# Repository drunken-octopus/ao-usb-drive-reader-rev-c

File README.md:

# ao-usb-drive-reader-rev-c
Revision C of the Aleph Objects USB reader ("green"), as originally archived from AlephObject's git repos in 2019.

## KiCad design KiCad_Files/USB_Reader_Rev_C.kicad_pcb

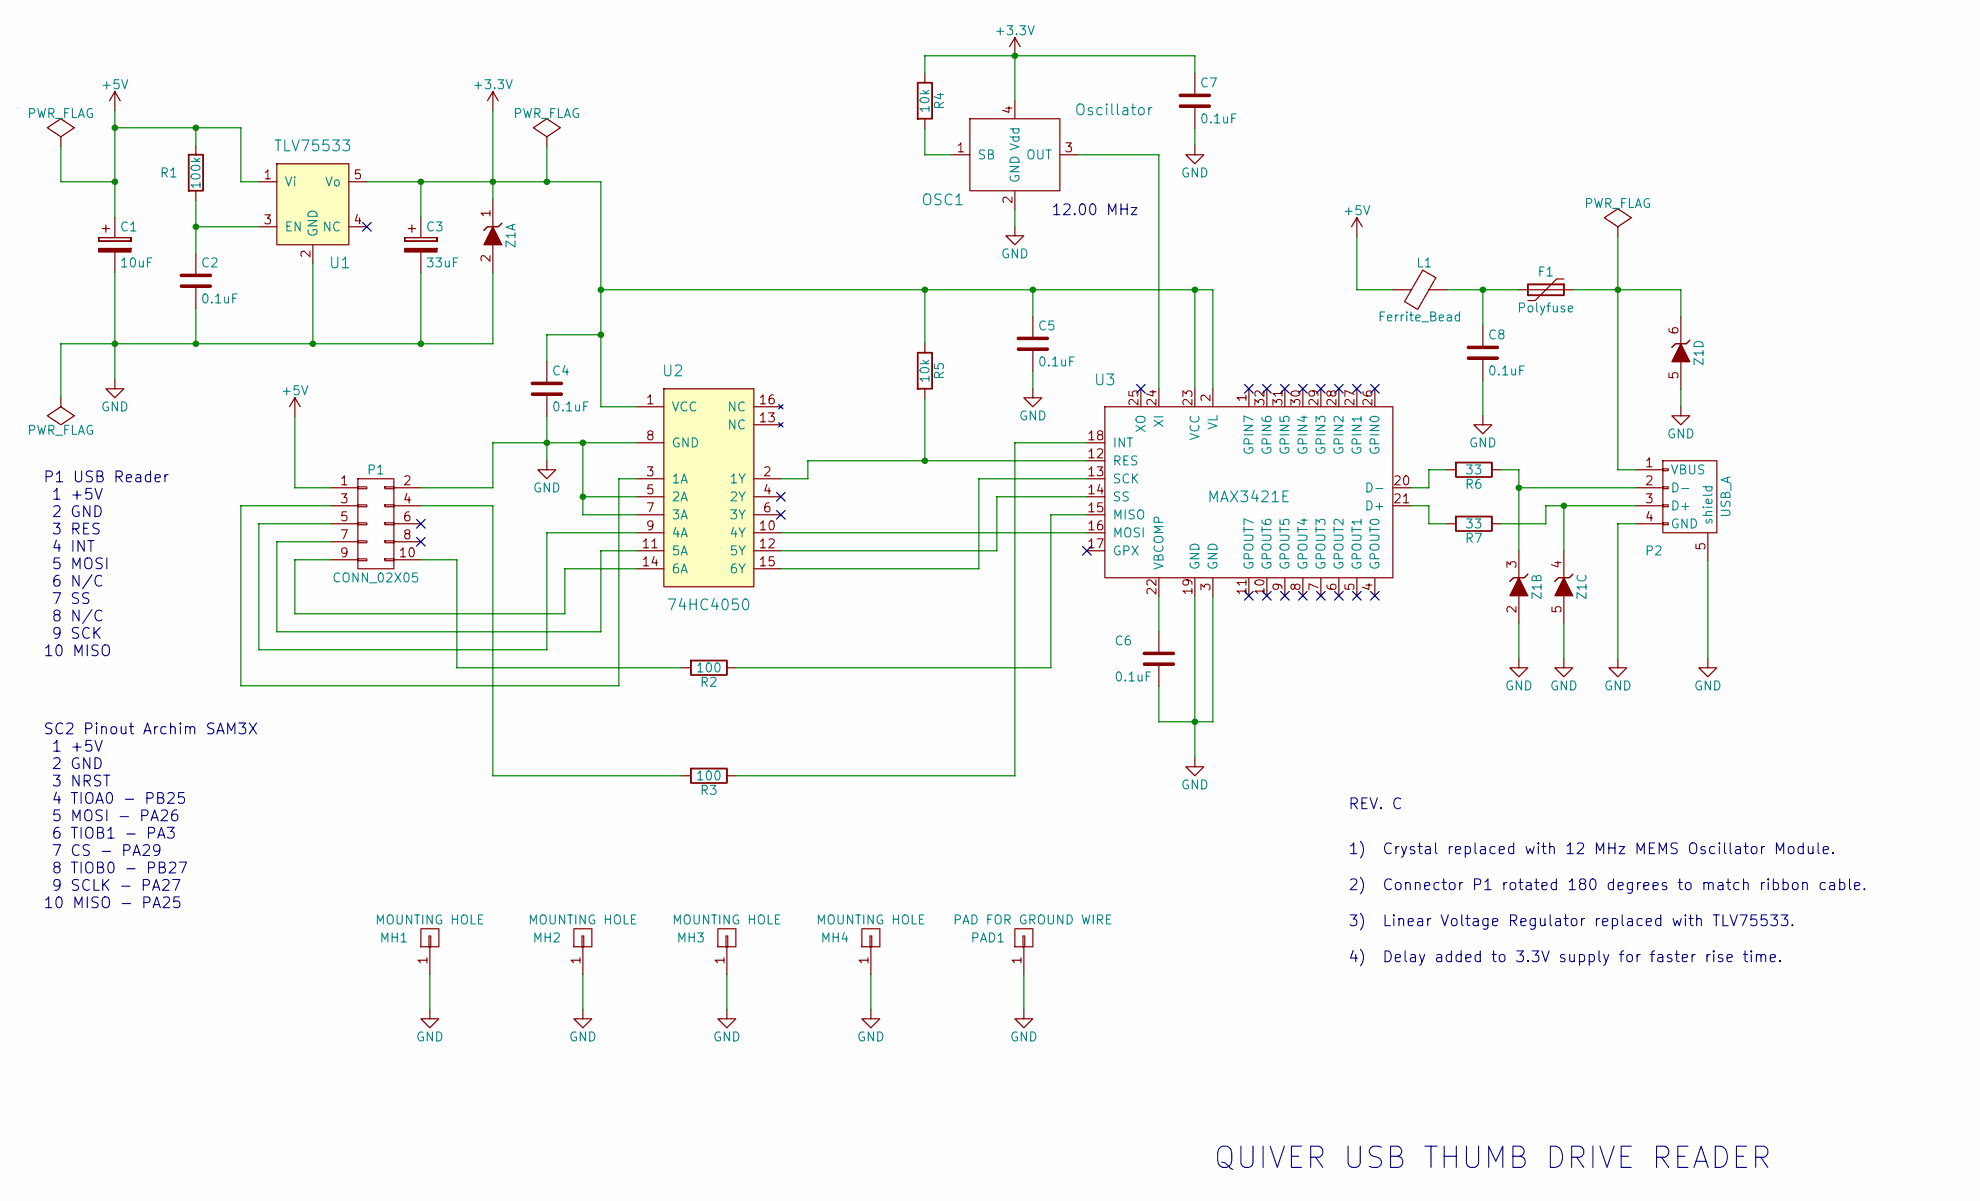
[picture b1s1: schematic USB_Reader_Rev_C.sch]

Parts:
C1: 10uF; TantalC_SizeD_EIA-7343_HandSoldering
C2, C4, C5, C6, C7, C8: 0.1uF; C_0603_HandSoldering
C3: 33uF; TantalC_SizeD_EIA-7343_HandSoldering
F1: Polyfuse; R_1206_HandSoldering
L1: Ferrite_Bead; C_0603_HandSoldering
MH1, MH2, MH3, MH4: MOUNTING HOLE; MH_M3x6mm
OSC1: Oscillator; FA-328_Crystal
P1: CONN_02X05; IDC_Header_Straight_10pins
P2: USB_A; USB_A_TH
PAD1: PAD FOR GROUND WIRE; GND_PAD
R1: 100k; R_0603_HandSoldering
R2, R3: 100; R_0603_HandSoldering
R4, R5: 10k; R_0603_HandSoldering
R6, R7: 33; R_0603_HandSoldering
U1: TLV75533; SOT-23-5
U2: 74HC4050; SO-16-N
U3: MAX3421E; LQFP-32_5x5mm_Pitch0.5mm
Z1: ZENER_4_CHANNEL; SOT-666

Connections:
+3V3: C3.1, C4.1, C5.1, C7.1, OSC1.4 (Vdd), R4.1, R5.1, U1.5 (Vo), U2.1 (VCC), U3.2 (VL), U3.23 (VCC), Z1.1 (K)
+5V: C1.1, L1.2, P1.1, R1.1, U1.1 (Vi)
GND: C1.2, C2.2, C3.2, C4.2, C5.2, C6.2, C7.2, C8.2, MH1.1, MH2.1, MH3.1, MH4.1, OSC1.2 (GND), P1.2, P2.4 (GND), P2.5 (shield), PAD1.1, U1.2 (GND), U2.5 (2A), U2.7 (3A), U2.8 (GND), U3.3 (GND), U3.19 (GND), Z1.2 (A), Z1.5 (A)
unnamed: C2.1, R1.2, U1.3 (EN)
unnamed: C6.1, U3.22 (VBCOMP)
unnamed: C8.1, F1.2, L1.1
unnamed: F1.1, P2.1 (VBUS), Z1.6 (K)
unnamed: OSC1.1 (SB), R4.2
unnamed: OSC1.3 (OUT), U3.24 (XI)
unnamed: P1.3, U2.3 (1A)
unnamed: P1.4, R3.2
unnamed: P1.5, U2.9 (4A)
unnamed: P1.7, U2.11 (5A)
unnamed: P1.9, U2.14 (6A)
unnamed: P1.10, R2.2
unnamed: P2.2 (D-), R6.1, Z1.3 (K)
unnamed: P2.3 (D+), R7.1, Z1.4 (K)
unnamed: R2.1, U3.15 (MISO)
unnamed: R3.1, U3.18 (INT)
unnamed: R5.2, U2.2 (1Y), U3.12 (RES)
unnamed: R6.2, U3.20 (D-)
unnamed: R7.2, U3.21 (D+)
unnamed: U2.10 (4Y), U3.16 (MOSI)
unnamed: U2.12 (5Y), U3.14 (SS)
unnamed: U2.15 (6Y), U3.13 (SCK)

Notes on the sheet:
QUIVER USB THUMB DRIVE READER
SC2 Pinout Archim SAM3X 1 +5V 2 GND 3 NRST 4 TIOA0 - PB25 5 MOSI - PA26 6 TIOB1 - PA3 7 CS - PA29 8 TIOB0 - PB27 9 SCLK - PA27 10 MISO - PA25
P1 USB Reader 1 +5V 2 GND 3 RES 4 INT 5 MOSI 6 N/C 7 SS 8 N/C 9 SCK 10 MISO
REV. C
1) Crystal replaced with 12 MHz MEMS Oscillator Module.
2) Connector P1 rotated 180 degrees to match ribbon cable.
12.00 MHz
3) Linear Voltage Regulator replaced with TLV75533.
4) Delay added to 3.3V supply for faster rise time.

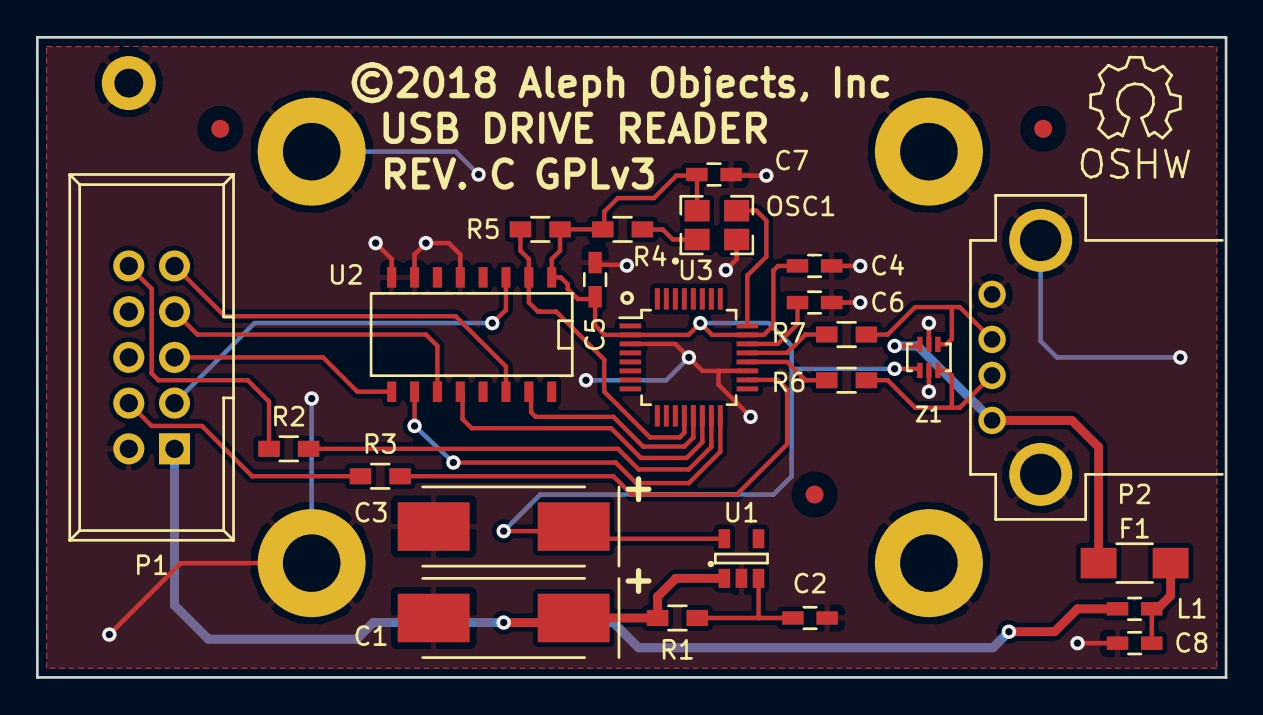
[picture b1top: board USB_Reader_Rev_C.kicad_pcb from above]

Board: 2 copper layers, 66.0 x 35.6 mm, 29 parts (0 on the bottom side), 25 nets.

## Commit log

2018-02-20 KiCad and Gerber files added for the first time to the repo.
2018-02-20 GIT Licenses added to the repo.
2018-04-19 Update License from AGPL to GPL
2018-08-24 Added REV A Gerbers
2018-08-24 Added REV A KiCad Files
2018-08-24 Removed REV A files
2018-08-24 Added REV B files
2018-10-29 C5 and C7 changed to 18pF on BOM
2018-11-21 Changed value of C5 and C7 to 18pF.
2018-11-26 Updated schematic pdf to show C5 and C7 as 18pF
2018-12-28 All board files updated to Rev. C
2019-01-10 OSHW mark added to PCB silk.
2023-07-22 Added PDF version of schematics

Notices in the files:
KiCad_Files/USB_Reader_Rev_C.kicad_pcb:
GPLv3
©2018 Aleph Objects, Inc
